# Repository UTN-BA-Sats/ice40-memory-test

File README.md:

# iCE40 memory tester
## Contents
* `firmware`: ESP32 firmware for interfacing with the FPGA
* `fpga_core`: Verilog files for the iCE40 core
* `esp32_board`: design files for interface board between ESP32 and FPGA

## Required hardware
* EDU-FPGA
* ESP32-DevKitC

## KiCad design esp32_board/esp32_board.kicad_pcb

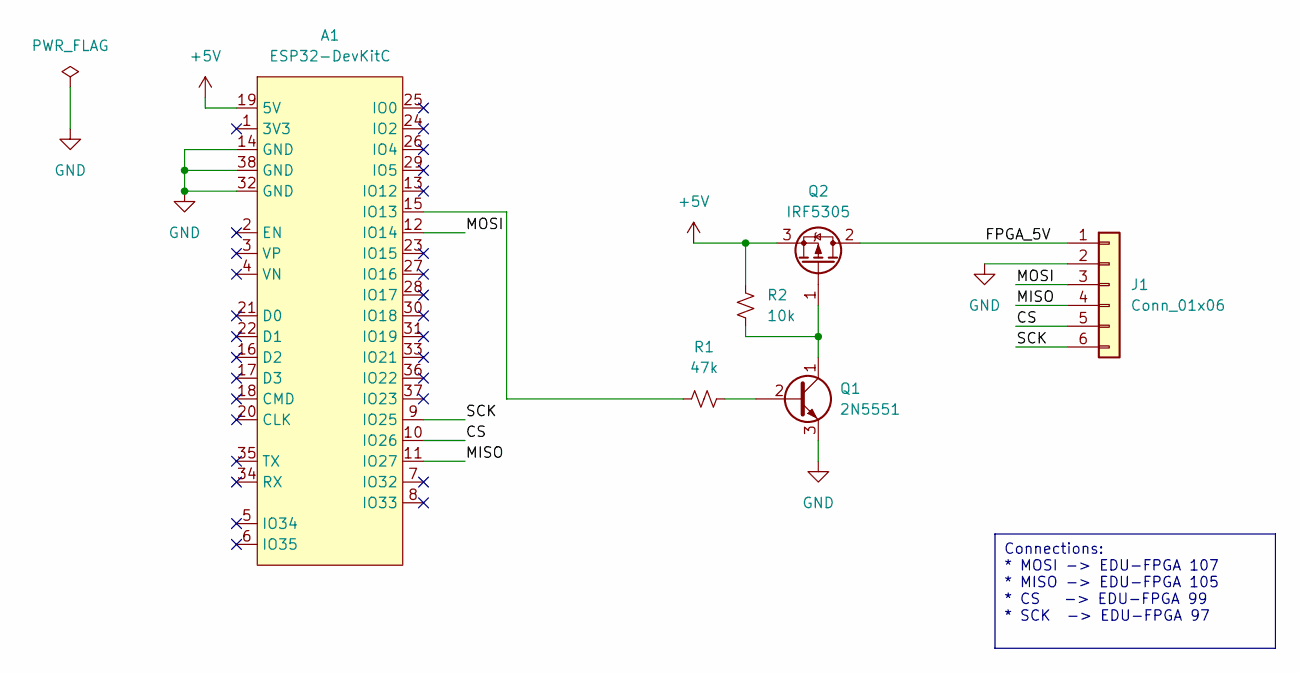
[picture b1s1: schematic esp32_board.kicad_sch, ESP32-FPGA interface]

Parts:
A1: ESP32-DevKitC; ESP32_DevkitC_V4
J1: Conn_01x06; PinSocket_1x06_P2.54mm_Vertical
Q1: 2N5551; TO-92
Q2: IRF5305; TO-220-3_Vertical
R1: 47k; R_Axial_DIN0207_L6.3mm_D2.5mm_P10.16mm_Horizontal
R2: 10k; R_Axial_DIN0207_L6.3mm_D2.5mm_P10.16mm_Horizontal

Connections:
+5V: A1.19 (5V), Q2.3 (S), R2.1
/CS: A1.10 (IO26), J1.5
/FPGA_5V: J1.1, Q2.2 (D)
/MISO: A1.11 (IO27), J1.4
/MOSI: A1.12 (IO14), J1.3
/SCK: A1.9 (IO25), J1.6
GND: A1.14 (GND), A1.32 (GND), A1.38 (GND), J1.2, Q1.3 (E)
unnamed: A1.15 (IO13), R1.1
unnamed: Q1.2 (B), R1.2
unnamed: Q1.1 (C), Q2.1 (G), R2.2

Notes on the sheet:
Connections: * MOSI -> EDU-FPGA 107 * MISO -> EDU-FPGA 105 * CS -> EDU-FPGA 99 * SCK -> EDU-FPGA 97

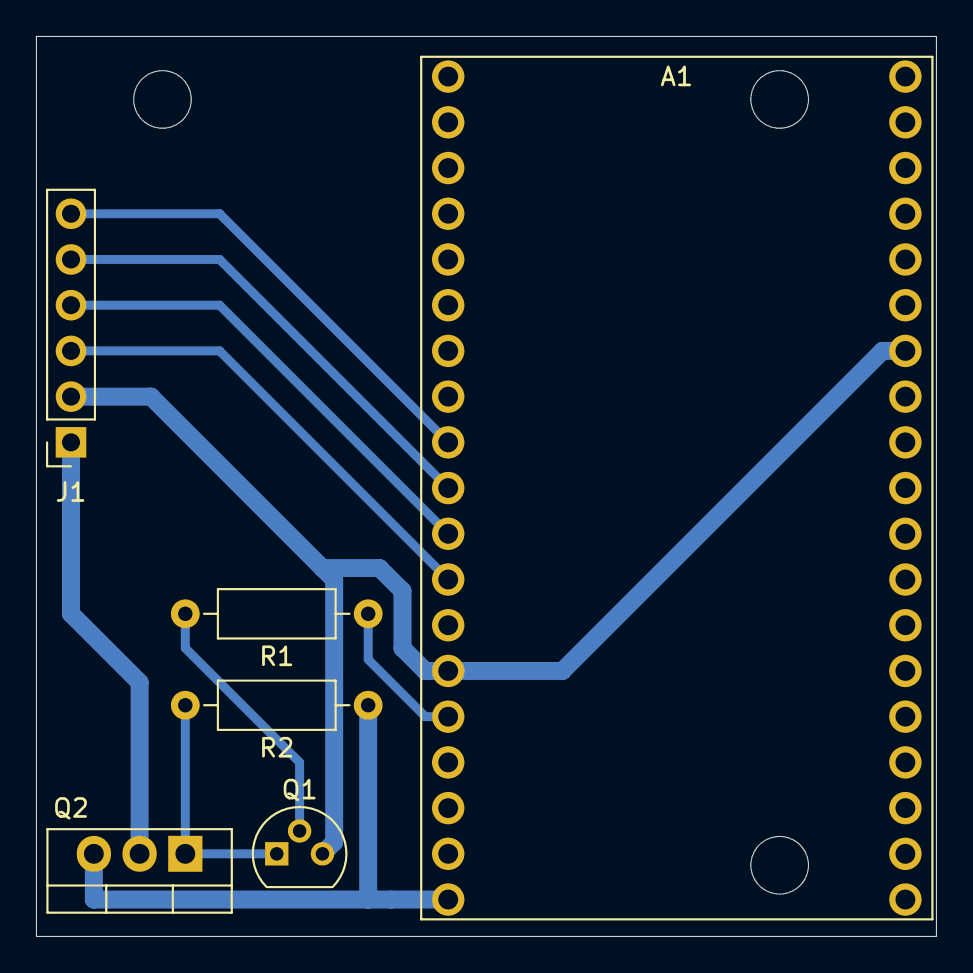
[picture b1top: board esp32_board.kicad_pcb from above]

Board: 2 copper layers, 50.0 x 50.0 mm, 6 parts (0 on the bottom side), 10 nets.

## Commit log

2024-10-06 Add ROM signature
2024-10-06 Add ESP32 firmware and README files
2024-10-06 Add circuit description
2024-10-13 Add board for communication between ESP32 and FPGA
2024-10-27 Update "Connections" text box
2024-10-27 Reduce PCB size to 50mmx50mm, set zone clearance to 1 mm
2024-10-27 Connect all GND pins
2024-11-04 Add mounting holes
2024-11-11 Add write to RAM functionality and switch to 512x8 SRAM
2024-11-11 Update tests
2024-11-11 Update gitignore
2024-12-03 Return to 256x16 memory
2024-12-03 Rewrite FPGA RAM when wrong data is received
2024-12-03 Add VS Code config
